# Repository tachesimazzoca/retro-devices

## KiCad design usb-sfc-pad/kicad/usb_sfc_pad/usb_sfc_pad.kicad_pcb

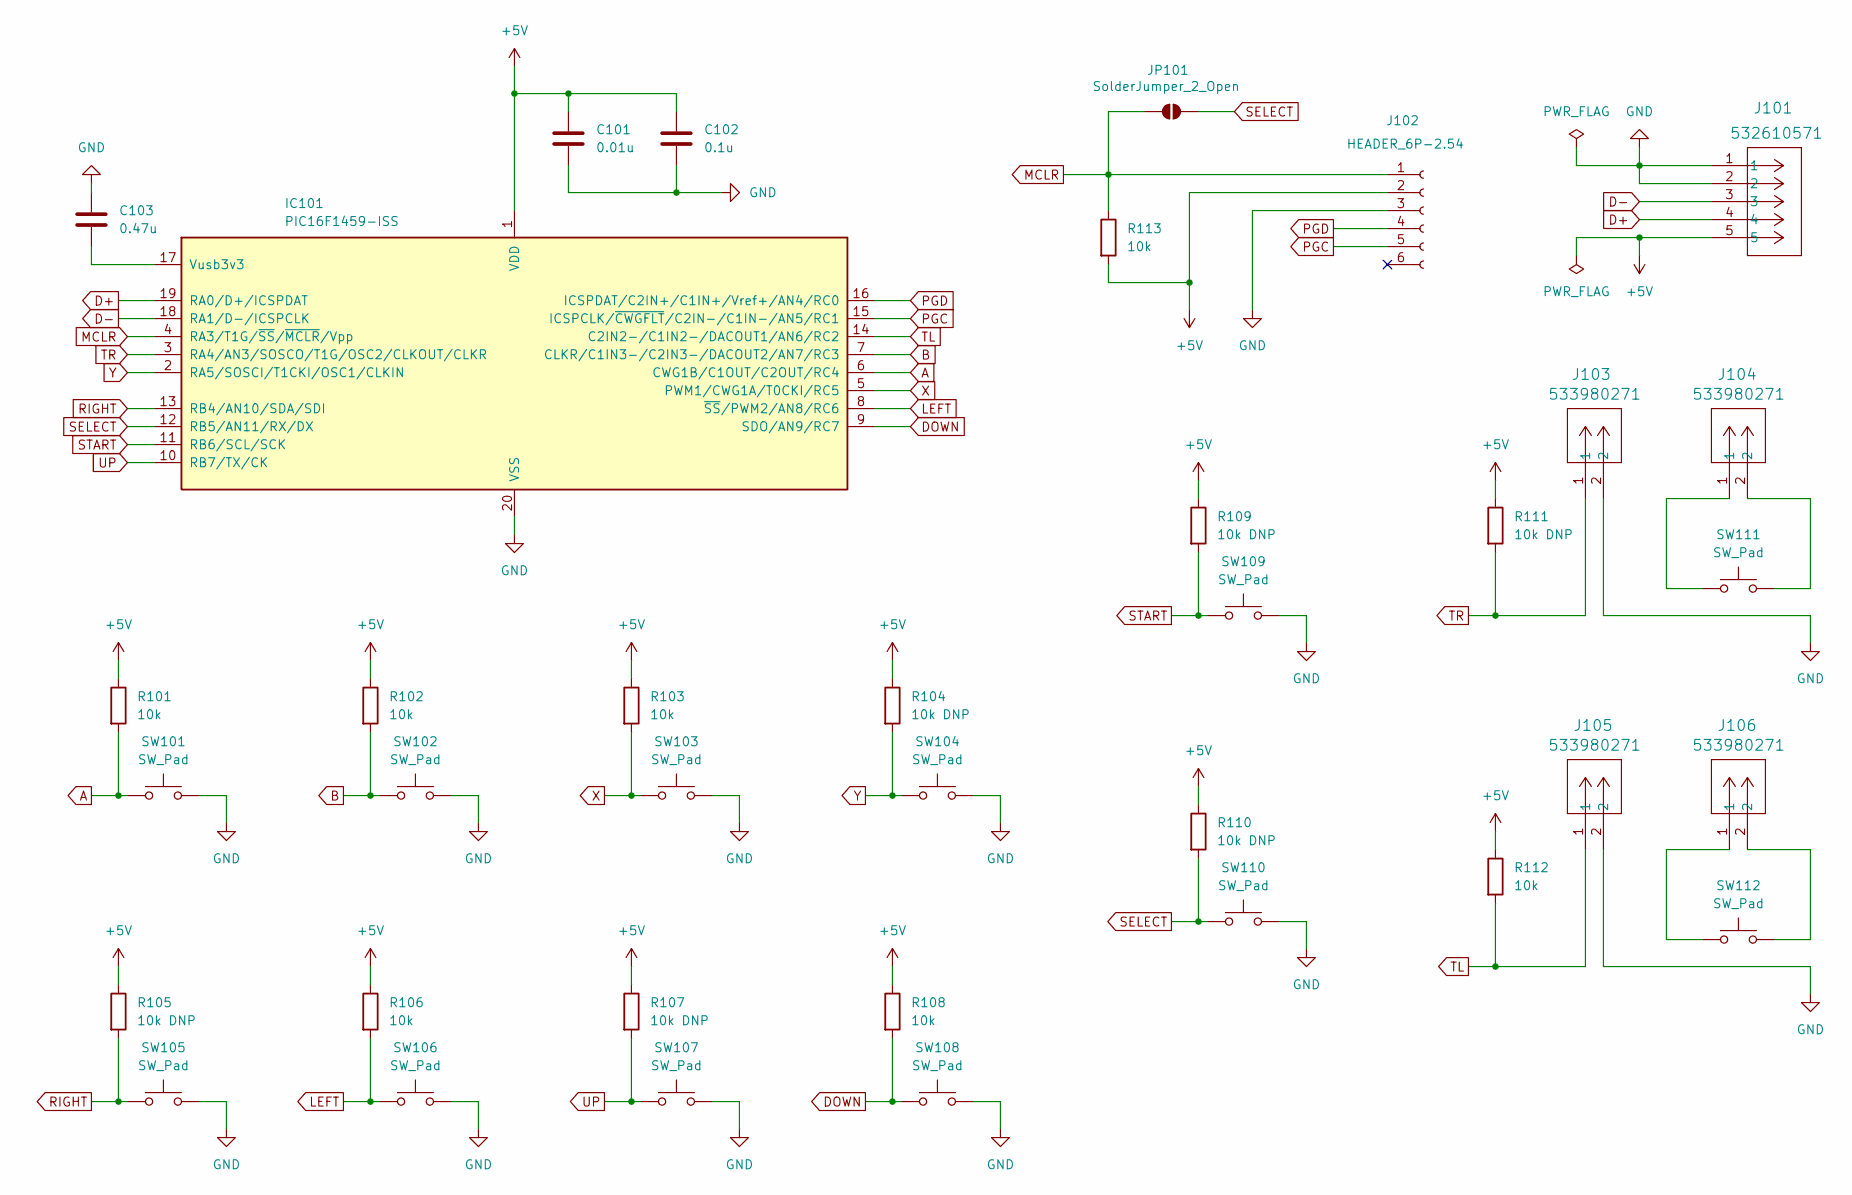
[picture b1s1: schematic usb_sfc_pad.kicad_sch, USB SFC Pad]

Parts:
C101: 0.01u; C_0402_1005Metric
C102: 0.1u; C_0402_1005Metric
C103: 0.47u; C_0402_1005Metric
IC101: PIC16F1459-ISS; SSOP-20_5.3x7.2mm_P0.65mm
J101: 532610571; CONN_532610001-SD_05_MOL
J102: HEADER_6P-2.54; PinHeader_1x06_P2.54mm_Vertical
J103, J104, J105, J106: 533980271; CONN02_533980271_MOL
JP101: SolderJumper_2_Open; SolderJumper-2_P1.3mm_Open_TrianglePad1.0x1.5mm
R101, R102, R103, R106, R108, R112, R113: 10k; R_0603_1608Metric
R104, R105, R107, R109, R110, R111: 10k DNP; R_0603_1608Metric
SW101, SW102, SW103, SW104, SW105, SW106, SW107, SW108, SW109, SW110, SW111, SW112: SW_Pad; SFC_Pad_F_NoSolder_5.5mm

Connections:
+5V: C101.1, C102.1, IC101.1 (VDD), J101.5, J102.2, R101.1, R102.1, R103.1, R104.1, R105.1, R106.1, R107.1, R108.1, R109.1, R110.1, R111.1, R112.1, R113.2
A: IC101.6 (CWG1B/C1OUT/C2OUT/RC4), R101.2, SW101.2
B: IC101.7 (CLKR/C1IN3-/C2IN3-/DACOUT2/AN7/RC3), R102.2, SW102.2
D+: IC101.19 (RA0/D+/ICSPDAT), J101.4
D-: IC101.18 (RA1/D-/ICSPCLK), J101.3
DOWN: IC101.9 (SDO/AN9/RC7), R108.2, SW108.1
GND: C101.2, C102.2, C103.1, IC101.20 (VSS), J101.1, J101.2, J102.3, J103.2, J105.2, SW101.1, SW102.1, SW103.1, SW104.1, SW105.2, SW106.1, SW107.2, SW108.2, SW109.2, SW110.2
LEFT: IC101.8 (~SS/PWM2/AN8/RC6), R106.2, SW106.2
MCLR: IC101.4 (RA3/T1G/~SS/~MCLR/Vpp), J102.1, JP101.1 (A), R113.1
unnamed: C103.2, IC101.17 (Vusb3v3)
unnamed: J104.1, SW111.1
unnamed: J104.2, SW111.2
unnamed: J106.1, SW112.1
unnamed: J106.2, SW112.2
PGC: IC101.15 (ICSPCLK/~CWGFLT/C2IN-/C1IN-/AN5/RC1), J102.5
PGD: IC101.16 (ICSPDAT/C2IN+/C1IN+/Vref+/AN4/RC0), J102.4
RIGHT: IC101.13 (RB4/AN10/SDA/SDI), R105.2, SW105.1
SELECT: IC101.12 (RB5/AN11/RX/DX), JP101.2 (B), R110.2, SW110.1
START: IC101.11 (RB6/SCL/SCK), R109.2, SW109.1
TL: IC101.14 (C2IN2-/C1IN2-/DACOUT1/AN6/RC2), J105.1, R112.2
TR: IC101.3 (RA4/AN3/SOSCO/T1G/OSC2/CLKOUT/CLKR), J103.1, R111.2
UP: IC101.10 (RB7/TX/CK), R107.2, SW107.1
X: IC101.5 (PWM1/CWG1A/T0CKI/RC5), R103.2, SW103.2
Y: IC101.2 (RA5/SOSCI/T1CKI/OSC1/CLKIN), R104.2, SW104.2

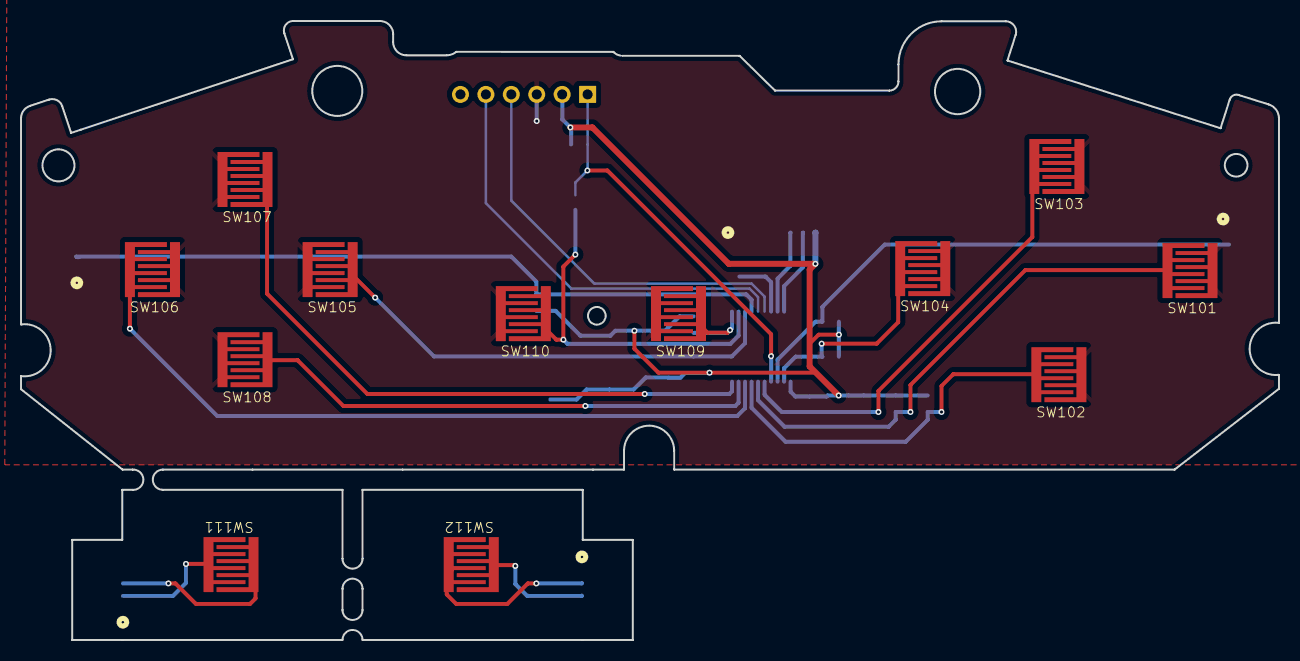
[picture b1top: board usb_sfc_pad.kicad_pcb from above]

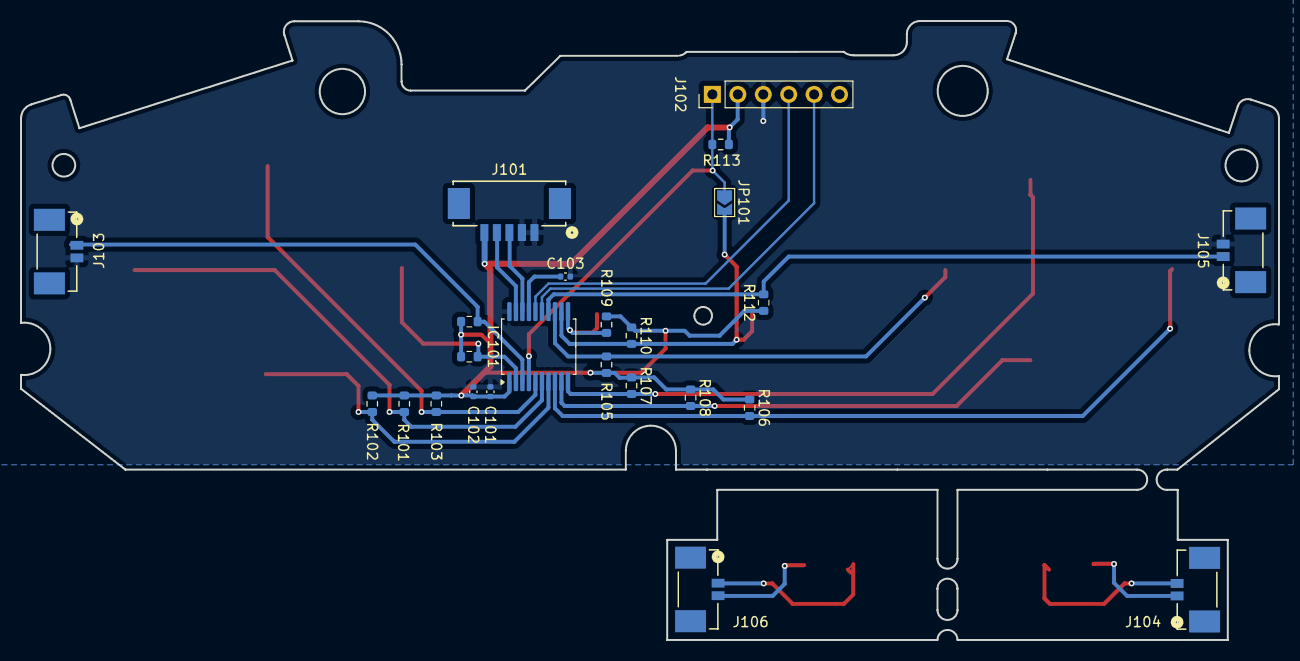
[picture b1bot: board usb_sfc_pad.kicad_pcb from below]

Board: 2 copper layers, 125.7 x 61.8 mm, 36 parts (24 on the bottom side), 24 nets.

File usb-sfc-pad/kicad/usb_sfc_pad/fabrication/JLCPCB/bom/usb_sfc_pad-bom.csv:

Comment,Designator,Footprint,LCSC Part #
10k,"R102,R112,R101,R113,R106,R108,R103",R_0603_1608Metric,C95204
0.01u,C101,C_0402_1005Metric,C85735
0.1u,C102,C_0402_1005Metric,C71629
0.47u,C103,C_0402_1005Metric,C126625
532610571,J101,CONN_532610001-SD_05_MOL,C17256390
533980271,"J103,J104,J105,J106",CONN02_533980271_MOL,C122410
PIC16F1459-ISS,IC101,SSOP-20_5.3x7.2mm_P0.65mm,C152208

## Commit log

2025-09-09 Add usb-sfc-pad
2025-09-10 Add footprint SFC_Pad
2025-09-15 Add PCB
    - Renumber SFC_Pad's pins
2025-09-15 Fix clearance in IC101 pads
2025-09-15 Add gerber configuration
2025-09-16 Add JLCPCB fabrication files
2025-09-17 Replace 532610671 with 532610571
2025-09-21 Combine LR board
2025-09-24 Replace right-angle 2pins with vertical ones
2025-09-26 Add PicoBlade 3D-models
2025-09-27 Igonre macOS files
2025-09-27 Fix LR connectors' placement
2025-12-29 Add schematic usb_sfc_pad.svg
